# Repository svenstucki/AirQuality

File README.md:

# AirQuality

AirQuality is an ESP32-C6 environmental sensor project with persistent history
storage, a WebBluetooth dashboard, and an accompanying KiCad board design.

## Components

- [`firmware/`](firmware/) — embedded Rust firmware for the ESP32-C6. It reads
  the connected environmental sensor modules, exposes live values and history
  over BLE, and controls the RGB LED.
- [`dashboard/`](dashboard/) — dependency-free standalone WebBLE dashboards for
  live sensor values and stored history. Run them from localhost in a browser
  with WebBluetooth support.
- [`hardware/`](hardware/) — KiCad project sources, local symbols and
  footprints, schematic documentation, and the committed fabrication archive.

## Quick start

### Firmware

```text
cd firmware
cargo embed
```

The default workflow uses a debug build and the ESP32-C6 USB-JTAG interface.
See [`firmware/README.md`](firmware/README.md) for sensor, BLE, storage, and
flashing details.

### Dashboards

Serve the dashboard directory from localhost, then open either HTML page in a
WebBluetooth-capable browser:

```text
cd dashboard
python3 -m http.server 8000
```

- [`air-quality.html`](dashboard/air-quality.html) — live sensor dashboard.
- [`air-quality-history.html`](dashboard/air-quality-history.html) — persistent
  history controls, retrieval, graphing, and CSV export.

### Hardware

Open [`hardware/AirQuality.kicad_pro`](hardware/AirQuality.kicad_pro)
with KiCad. The project README documents the module interconnects and layout
considerations. The fabrication archive and generated schematic PDF are in
[`hardware/fabrication/`](hardware/fabrication/).

## Security

The BLE services are unauthenticated: any nearby device can read the sensor
values, change the LED color, set the clock, and erase the stored history.
Treat the device as suitable for trusted environments only.

## License

- Firmware and dashboards: [MIT License](LICENSE).
- Hardware design files and fabrication artifacts in [`hardware/`](hardware/):
  [CERN Open Hardware Licence Version 2 - Permissive](hardware/LICENSE)
  (CERN-OHL-P-2.0).

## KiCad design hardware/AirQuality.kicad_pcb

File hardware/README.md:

# AirQuality KiCad Project

KiCad 9 PCB project for an ESP32-C6-based air-quality sensor board. The board
combines several prebuilt modules on one PCB and connects them through one shared
3.3 V I2C bus.

## Project Files

- `AirQuality.kicad_pro`: KiCad 9 project file.
- `AirQuality.kicad_sch`: root schematic with all modules, shared I2C wiring,
  power symbols, and I2C pull-up resistors.
- `AirQuality.kicad_pcb`: routed PCB layout with the six module footprints,
  the two pull-up resistors, and M3 mounting holes.
- `fabrication/`: dated Gerber/drill archives and matching schematic PDFs for
  each tapeout. The most recent date supersedes the earlier ones.

The design notes below record the reasoning behind the board and are useful
when adapting it to different modules.

## Modules

| Module | Role | Interface | Expected I2C address |
| --- | --- | --- | --- |
| Nano ESP32-C6 development board | MCU, Wi-Fi/BLE/802.15.4 controller | I2C master | N/A |
| DS3231 RTC module for Raspberry Pi, 5-pin header | Real-time clock | I2C | `0x68` |
| SGP41 module | VOC/NOx gas sensor | I2C | `0x59` |
| SCD41 module | CO2 sensor | I2C | `0x62` |
| SHT41 module | Temperature/humidity sensor | I2C | `0x44` |
| BMP580 module | Barometric pressure sensor | I2C | `0x47` default, `0x46` selectable |

There are no address conflicts in this set.

## Project Libraries

The project has local module libraries at the project root:

- `AirQuality.kicad_sym`: schematic symbols for each module.
- `AirQuality.pretty/`: footprint library with one footprint per module.
- `sym-lib-table` and `fp-lib-table`: project-local KiCad library tables.

Each footprint models a breakout module as a whole rather than the bare sensor
IC: the pin-header pads at 2.54 mm pitch plus the module body outline.

| Footprint | Body | Header |
| --- | --- | --- |
| Nano ESP32-C6 | 28 mm x 46 mm, plus 18 mm x 8 mm antenna protrusion | two 1x15 rows, 25.4 mm apart |
| DS3231 RTC | 14 mm x 14 mm | 1x05 |
| SGP41 | 13 mm x 10 mm | 1x04 |
| SCD41 | 22 mm x 13 mm | 1x04 |
| SHT41 | 12 mm x 10 mm | 1x04 |
| BMP580 | 14 mm x 10 mm | two 1x04 rows, 12 mm apart |

Breakout modules for the same sensor differ between vendors. Check these
dimensions and the pin order against the modules you have before ordering
boards.

The DS3231 RTC symbol intentionally exposes only four functional schematic pins,
but its assigned footprint is a 1x05 header. Physical header pin 4 is present and
left unconnected; the symbol maps its fourth functional pin to footprint pad 5.

## Electrical Intent

- Use one shared bus: `I2C_SDA`, `I2C_SCL`, `3V3`, and `GND`.
- Keep all I2C pull-ups tied to `3V3`, not `5V`.
- The schematic includes `R1` and `R2` as `4.7k` pull-ups from `I2C_SDA` and
  `I2C_SCL` to `3V3` using 0603 SMD footprints.
- Check each module for already-populated pull-up resistors. Multiple breakout
  boards often each include pull-ups, which can make the effective pull-up too
  strong when combined.
- Observed module pull-ups:

  | Module | Populated I2C pull-ups |
  | --- | --- |
  | DS3231 RTC module | `4.3k` on SDA and SCL |
  | SHT41 temperature/humidity module | `10k` on SDA and SCL |
  | SCD41 CO2 module | `10k` on SDA and SCL |
  | BMP580 pressure module | `10k` on SDA and SCL |
  | SGP41 gas module | none observed |

  With these modules installed, the effective bus pull-up is about `1.9k` per
  line before adding schematic `R1`/`R2`; treat `R1` and `R2` as DNP unless the
  module pull-ups are removed or the bus rise time proves too slow.
- Target standard-mode or fast-mode I2C. The DS3231 supports fast-mode I2C
  operation; sensor breakouts should still be checked against their module
  documentation.
- Prefer powering every module from `3V3` unless the exact module documentation
  proves that another supply arrangement is required and does not pull SDA/SCL
  above 3.3 V.
- The board has no onboard power source or regulator; power arrives through
  the module headers. ERC `power_pin_not_driven` messages are therefore
  expected, and the schematic deliberately has no `PWR_FLAG` symbols to
  silence them.

## ESP32-C6 Pin Notes

The local Nano ESP32-C6 symbol and footprint use side-aware KiCad pin/pad
numbers: `L1`-`L15` for the left side top-to-bottom and `R1`-`R15` for the right
side top-to-bottom. This avoids duplicate `1`-`15` pin numbers while matching
the module pin tables.

The firmware uses GPIO6 for SDA and GPIO7 for SCL, which are also the
low-power I2C pins on Espressif reference development boards.

When substituting a different ESP32-C6 board, do not rely on Arduino-style
labels alone. Confirm:

- Which header pins expose GPIO6 and GPIO7.
- Header pitch, row spacing, board outline, USB-C keepout, antenna keepout, and
  mounting constraints.
- Whether the Nano board regulator can supply all attached modules with enough
  margin, especially during wireless transmit current peaks.

## Schematic Guidance

Use connector or module symbols rather than bare IC symbols unless the design is
changed to place the sensors directly on this PCB.

Suggested net names:

- `3V3`
- `GND`
- `I2C_SDA`
- `I2C_SCL`
- Optional: `RTC_INT` or `RTC_SQW` if the DS3231 alarm/square-wave output is
  used later.

Add test points for `3V3`, `GND`, `I2C_SDA`, and `I2C_SCL` if there is room.

## PCB Layout Guidance

- Place the ESP32-C6 antenna area at a board edge with a copper/component keepout
  matching the Nano board vendor guidance.
- Keep environmental sensors away from heat sources such as regulators, USB power
  circuitry, and the ESP32-C6 module when practical.
- Give SCD41, SGP41, SHT41, and BMP580 modules exposure to ambient air. Avoid
  burying them under the MCU board or next to tall connectors that block airflow.
- Keep I2C traces short and direct. This board is module-to-module, so routing is
  expected to be low-speed and uncomplicated.
- Add silkscreen labels for module orientation and the four shared bus pins.

## Source References

- Nano ESP32-C6 development board:
  https://www.tindie.com/products/johnnywu/nanoesp32-c6-development-board/
- ESP32-C6 reference pin functions:
  https://docs.espressif.com/projects/esp-dev-kits/en/latest/esp32c6/esp32-c6-devkitc-1/user_guide.html
- DS3231 product page and datasheet:
  https://www.analog.com/en/products/ds3231.html
- Sensirion SGP41:
  https://sensirion.com/products/catalog/SGP41
- Sensirion SCD4x embedded driver address definition:
  https://github.com/Sensirion/embedded-i2c-scd4x
- Sensirion SHT41:
  https://sensirion.com/products/catalog/SHT41
- Bosch BMP580:
  https://www.bosch-sensortec.com/en/products/environmental-sensors/pressure-sensors/bmp580
- Adafruit BMP58xx breakout pinout notes:
  https://learn.adafruit.com/adafruit-bmp580-bmp581-and-bmp585-temperature-and-pressure-sensor/pinouts

## Licence

The hardware design files in this directory are licensed under the
[CERN Open Hardware Licence Version 2 - Permissive](LICENSE) (CERN-OHL-P-2.0).

Copyright (c) 2026 Sven Stucki

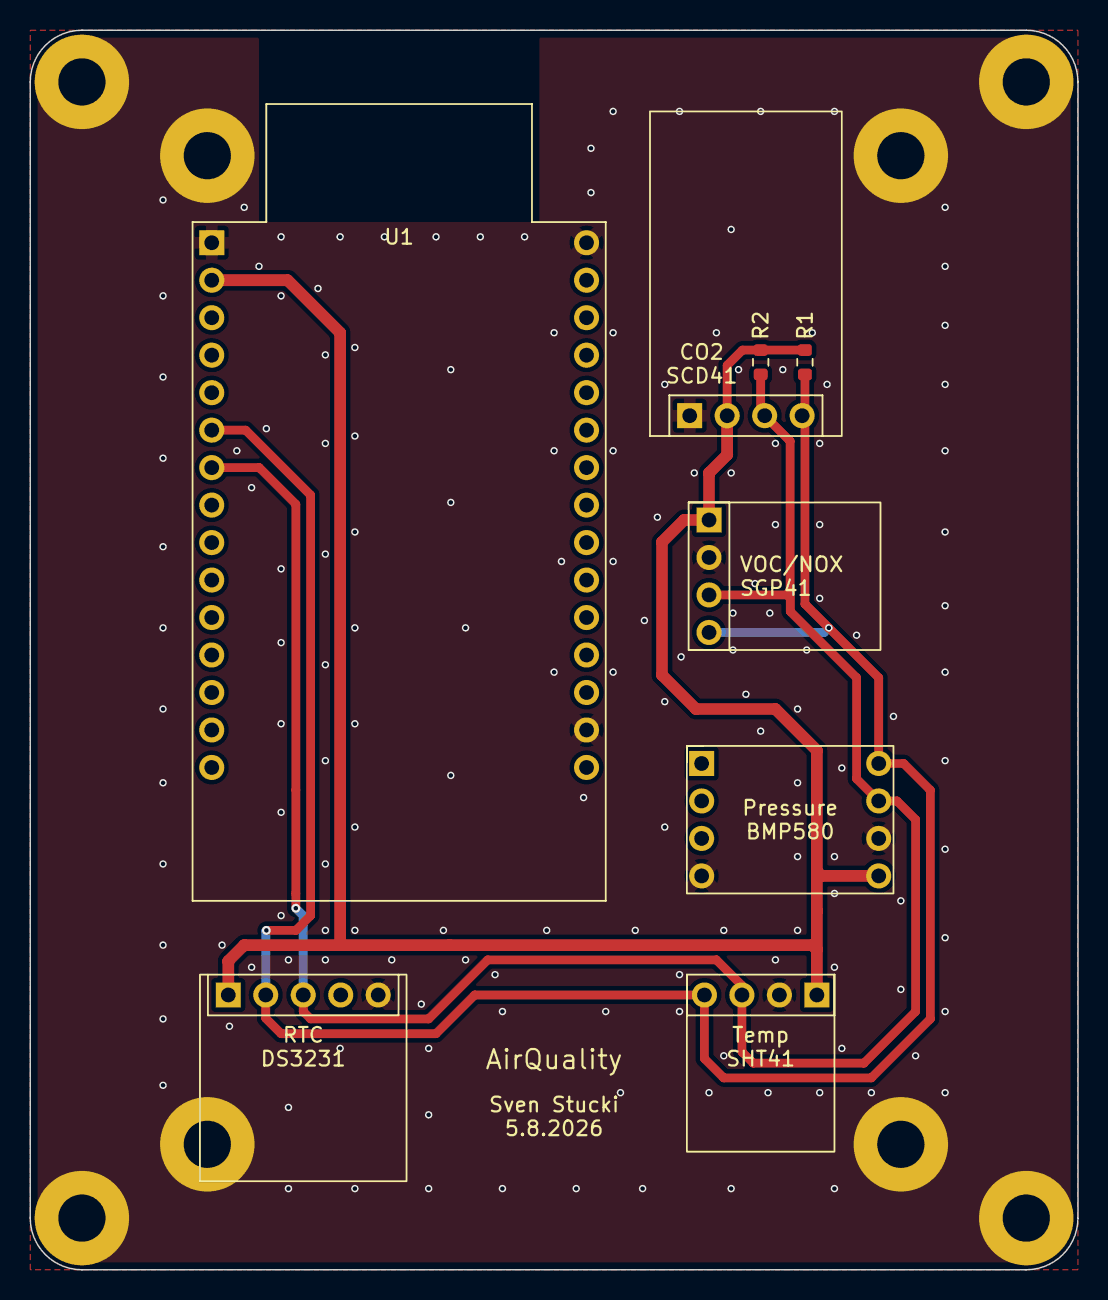
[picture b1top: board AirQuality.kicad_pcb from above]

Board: 2 copper layers, 71.0 x 84.0 mm, 16 parts (0 on the bottom side), 5 nets.

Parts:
H1, H2, H3, H4, H5, H6, H7, H8: MountingHole_Pad; MountingHole_3.2mm_M3_Pad
R1, R2: 4.7k; R_0603_1608Metric
U1: NanoESP32-C6_Module; NanoESP32-C6_Module_2x15_P2.54mm_Vertical
U2: DS3231_RTC_Module; DS3231_RTC_Module_1x05_P2.54mm_Vertical
U3: SGP41_Gas_Module; SGP41_Gas_Module_1x04_P2.54mm_Vertical
U4: SHT41_TempHumidity_Module; SHT41_TempHumidity_Module_1x04_P2.54mm_Vertical
U5: SCD41_CO2_Module; SCD41_CO2_Module_1x04_P2.54mm_Vertical
U6: BMP580_Pressure_Module; BMP580_Pressure_Module_2x04_P2.54mm_Vertical

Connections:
+3V3: R1.1, R2.1, U1.L2 (3V3), U2.1 (VCC), U3.1 (VIN), U4.1 (VIN), U5.2 (VDD), U6.8 (VCC)
+5V: U1.L15 (5V), U1.R15 (5V)
/I2C_SCL: R2.2, U1.L7 (GPIO7), U2.3 (SCL), U3.3 (SCL), U4.3 (SCL), U5.3 (SCL), U6.4 (SCL)
/I2C_SDA: R1.2, U1.L6 (GPIO6), U2.2 (SDA), U3.4 (SDA), U4.4 (SDA), U5.4 (SDA), U6.2 (SDA)
GND: H1.1, H2.1, H3.1, H4.1, H5.1, H6.1, H7.1, H8.1, U1.L1 (GND), U1.R1 (GND), U1.R14 (GND), U2.5 (GND), U3.2 (GND), U4.2 (GND), U5.1 (GND), U6.6 (GND), U6.7 (GND)
